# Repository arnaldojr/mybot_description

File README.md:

# mybot_description turtlebot3 Insper

Modelo 3d para simulador Gazebo do robô turtlebot3 com implementações do robô físico do curso de robótica computacional da engenharia de computação Insper.

## Desenvolvido por: Laboratório de informática, lab404.

# Como subir corretamente o robo com a garra no mapa do projeto.

## Atualize os repositorios "my_simulation", "mybot_description" e "robot202" .

    cd ~/catkin_ws/src/my_simulation/ 
    git checkout master
    git stash
    git pull
    cd ~/catkin_ws/src/mybot_descripton
    git checkout master
    git stash
    git pull
    cd ~/catkin_ws/src/robot202
    git pull
    cd ~/catkin_ws
    catkin_make
 
 ## Configure o arquivo .bashrc.
    
    cd ~
    code .bashrc

### Garanta que a configuração das linhas 119 ate 130 estão conforme abaixo:

    #############
    # Robotica  #
    #############

    export IPBerry=192.168.50.35
    # CANCELE  com # as linhas ROS_MASTER_URI  e ROS_IP se estiver usando com Gazebo, Sphinx ou Bebop
    #export ROS_MASTER_URI="http://"$IPBerry":11311" 
    #export ROS_IP=192.168.50.64

    #escolha qual o modelo robo sera usado no simulador
    export TURTLEBOT3_MODEL=burger 
    #export TURTLEBOT3_MODEL=waffle_pi

## Feche todos os terminais e abra um terminal novo

Cada comando deve ser executado em um terminal novo

### abra o mapa do gazebo

    roslaunch my_simulation pista_s.launch
    
### Habilitar controles da garra

    roslaunch mybot_description mybot_control2.launch     
 
### Execute seu codigo python

    rosrun ..........................................

### Como controlar a garra do robô:

A garra do robo é composta de duas partes - braço, pinça- cada parte possui uma articulação, são nestas articulações que atuamos para movimentação.

Joint1 = braço da garra. Valores máximos:

    Garra recolhida: -1.5
    Garra para frente: 0
    Garra levantada: 1.5
    
    rostopic pub -1 /joint1_position_controller/command std_msgs/Float64 "data: 0"

Joint2 = Pinça da garra com mimica (joint2 e joint3 juntos)

    Pinça fechada: 0
    Pinça aberta: -1

    rostopic pub -1 /joint2_position_controller/command std_msgs/Float64 "data: 0"

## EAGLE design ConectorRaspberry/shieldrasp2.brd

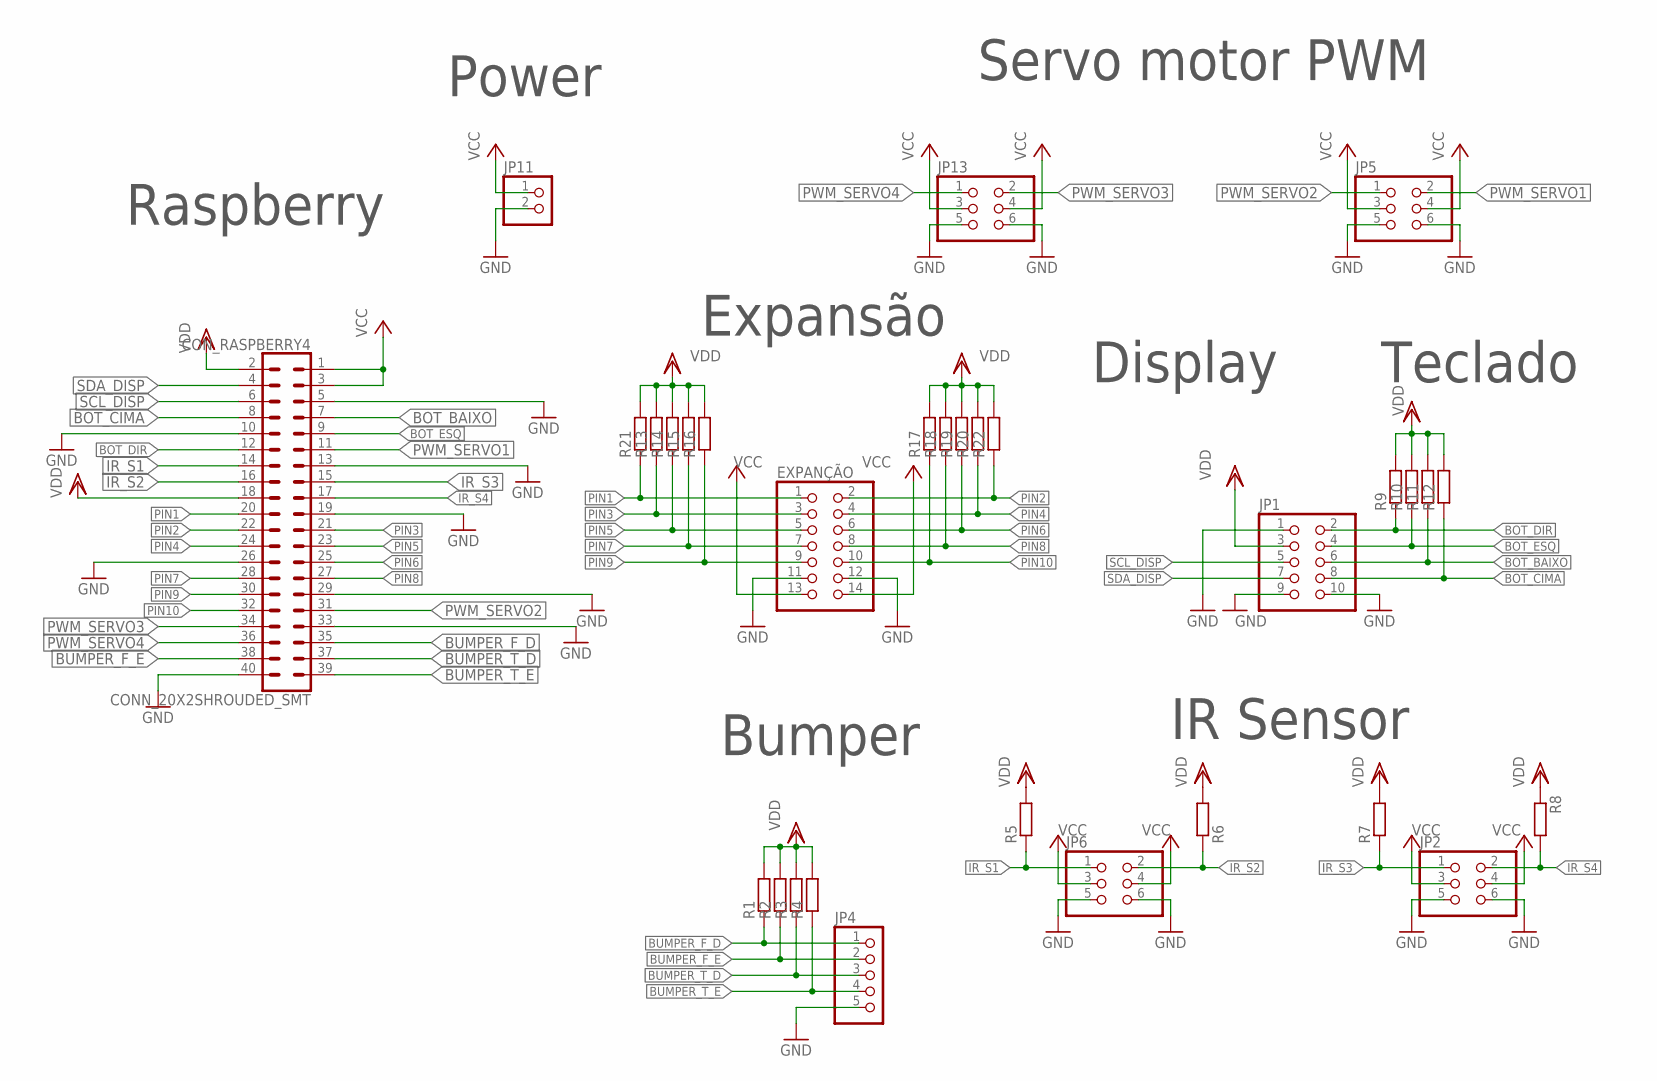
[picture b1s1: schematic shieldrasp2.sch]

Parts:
CON_RASPBERRY4: CONN_20X2SHROUDED_SMT; 2X20_SHROUDED_SMT
EXPANÇÃO: PINHD-2X7; 2X07
JP1: PINHD-2X5/90; 2X05/90
JP2, JP5, JP6, JP13: PINHD-2X3/90; 2X03/90
JP4: PINHD-1X5/90; 1X05/90
JP11: PINHD-1X2/90; 1X02/90
R1, R2, R3, R4, R5, R6, R7, R8, R9, R10, R11, R12, R13, R14, R15, R16, R17, R18, R19, R20, R21, R22: R-EU_M0805; M0805

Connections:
BOT_BAIXO: CON_RASPBERRY4.7, JP1.6, R11.1
BOT_CIMA: CON_RASPBERRY4.8, JP1.8, R12.1
BOT_DIR: CON_RASPBERRY4.12, JP1.2, R9.1
BOT_ESQ: CON_RASPBERRY4.9, JP1.4, R10.1
BUMPER_F_D: CON_RASPBERRY4.35, JP4.1, R1.1
BUMPER_F_E: CON_RASPBERRY4.38, JP4.2, R2.1
BUMPER_T_D: CON_RASPBERRY4.37, JP4.3, R3.1
BUMPER_T_E: CON_RASPBERRY4.39, JP4.4, R4.1
GND: CON_RASPBERRY4.5, CON_RASPBERRY4.10, CON_RASPBERRY4.13, CON_RASPBERRY4.19, CON_RASPBERRY4.26, CON_RASPBERRY4.29, CON_RASPBERRY4.33, CON_RASPBERRY4.40, EXPANÇÃO.11, EXPANÇÃO.12, JP1.1, JP1.9, JP1.10, JP2.5, JP2.6, JP4.5, JP5.5, JP5.6, JP6.5, JP6.6, JP11.2, JP13.5, JP13.6
IR_S1: CON_RASPBERRY4.14, JP6.1, R5.1
IR_S2: CON_RASPBERRY4.16, JP6.2, R6.1
IR_S3: CON_RASPBERRY4.15, JP2.1, R7.1
IR_S4: CON_RASPBERRY4.17, JP2.2, R8.2
PIN1: CON_RASPBERRY4.20, EXPANÇÃO.1, R21.1
PIN2: CON_RASPBERRY4.22, EXPANÇÃO.2, R22.1
PIN3: CON_RASPBERRY4.21, EXPANÇÃO.3, R13.1
PIN4: CON_RASPBERRY4.24, EXPANÇÃO.4, R20.1
PIN5: CON_RASPBERRY4.23, EXPANÇÃO.5, R14.1
PIN6: CON_RASPBERRY4.25, EXPANÇÃO.6, R19.1
PIN7: CON_RASPBERRY4.28, EXPANÇÃO.7, R15.1
PIN8: CON_RASPBERRY4.27, EXPANÇÃO.8, R18.1
PIN9: CON_RASPBERRY4.30, EXPANÇÃO.9, R16.1
PIN10: CON_RASPBERRY4.32, EXPANÇÃO.10, R17.1
PWM_SERVO1: CON_RASPBERRY4.11, JP5.2
PWM_SERVO2: CON_RASPBERRY4.31, JP5.1
PWM_SERVO3: CON_RASPBERRY4.34, JP13.2
PWM_SERVO4: CON_RASPBERRY4.36, JP13.1
SCL_DISP: CON_RASPBERRY4.6, JP1.5
SDA_DISP: CON_RASPBERRY4.4, JP1.7
VCC: CON_RASPBERRY4.1, CON_RASPBERRY4.3, EXPANÇÃO.13, EXPANÇÃO.14, JP2.3, JP2.4, JP5.3, JP5.4, JP6.3, JP6.4, JP11.1, JP13.3, JP13.4
VDD: CON_RASPBERRY4.2, CON_RASPBERRY4.18, JP1.3, R1.2, R2.2, R3.2, R4.2, R5.2, R6.2, R7.2, R8.1, R9.2, R10.2, R11.2, R12.2, R13.2, R14.2, R15.2, R16.2, R17.2, R18.2, R19.2, R20.2, R21.2, R22.2

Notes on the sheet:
Servo motor PWM
Raspberry
Display
Teclado
Bumper
IR Sensor
Power
Expansão

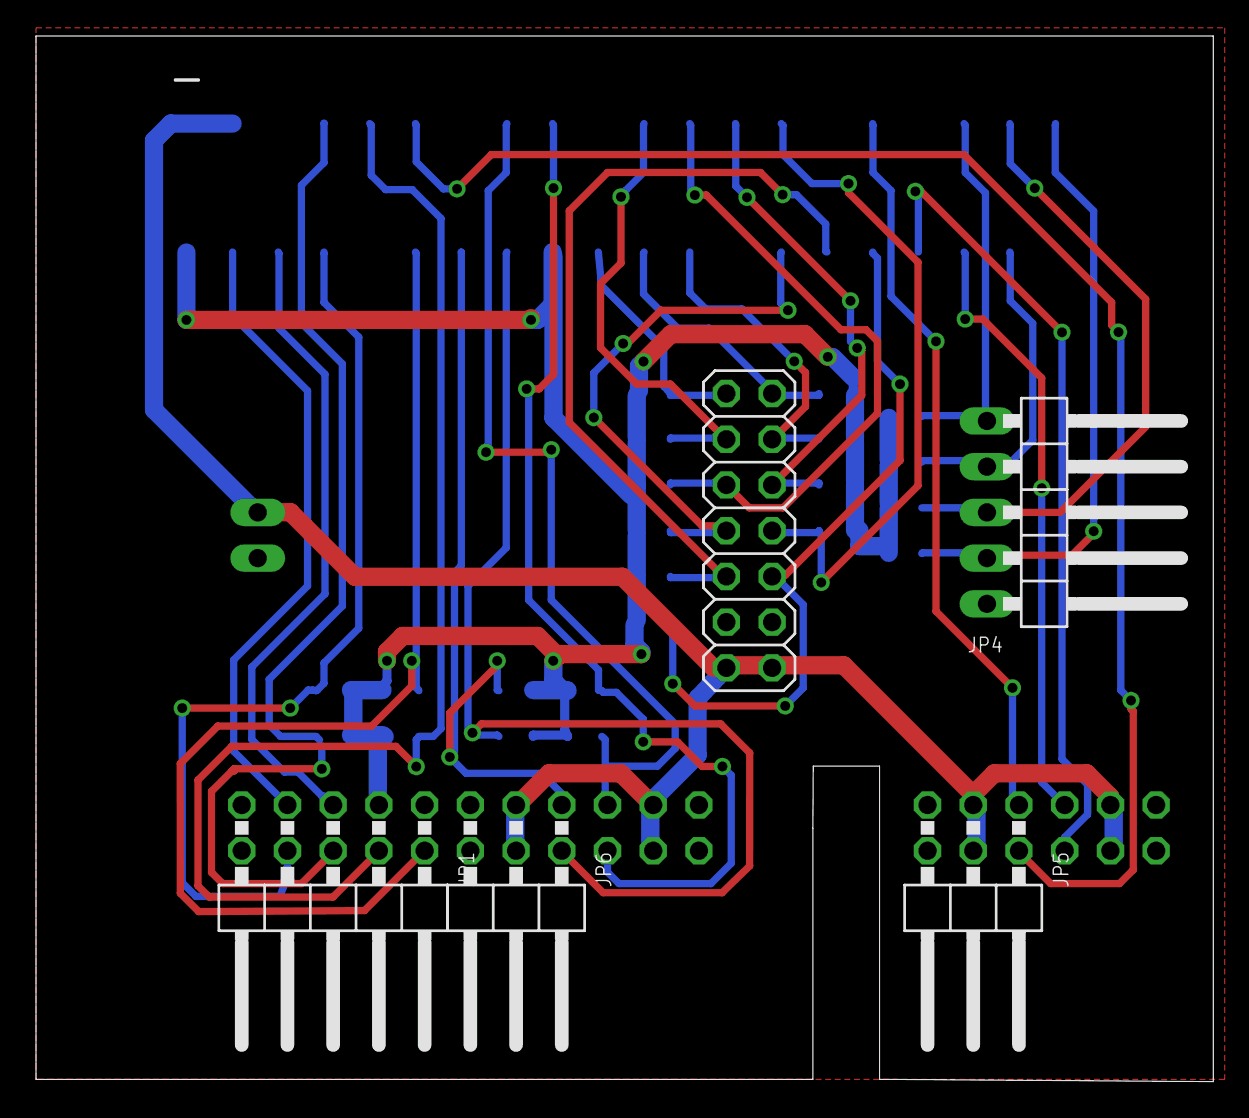
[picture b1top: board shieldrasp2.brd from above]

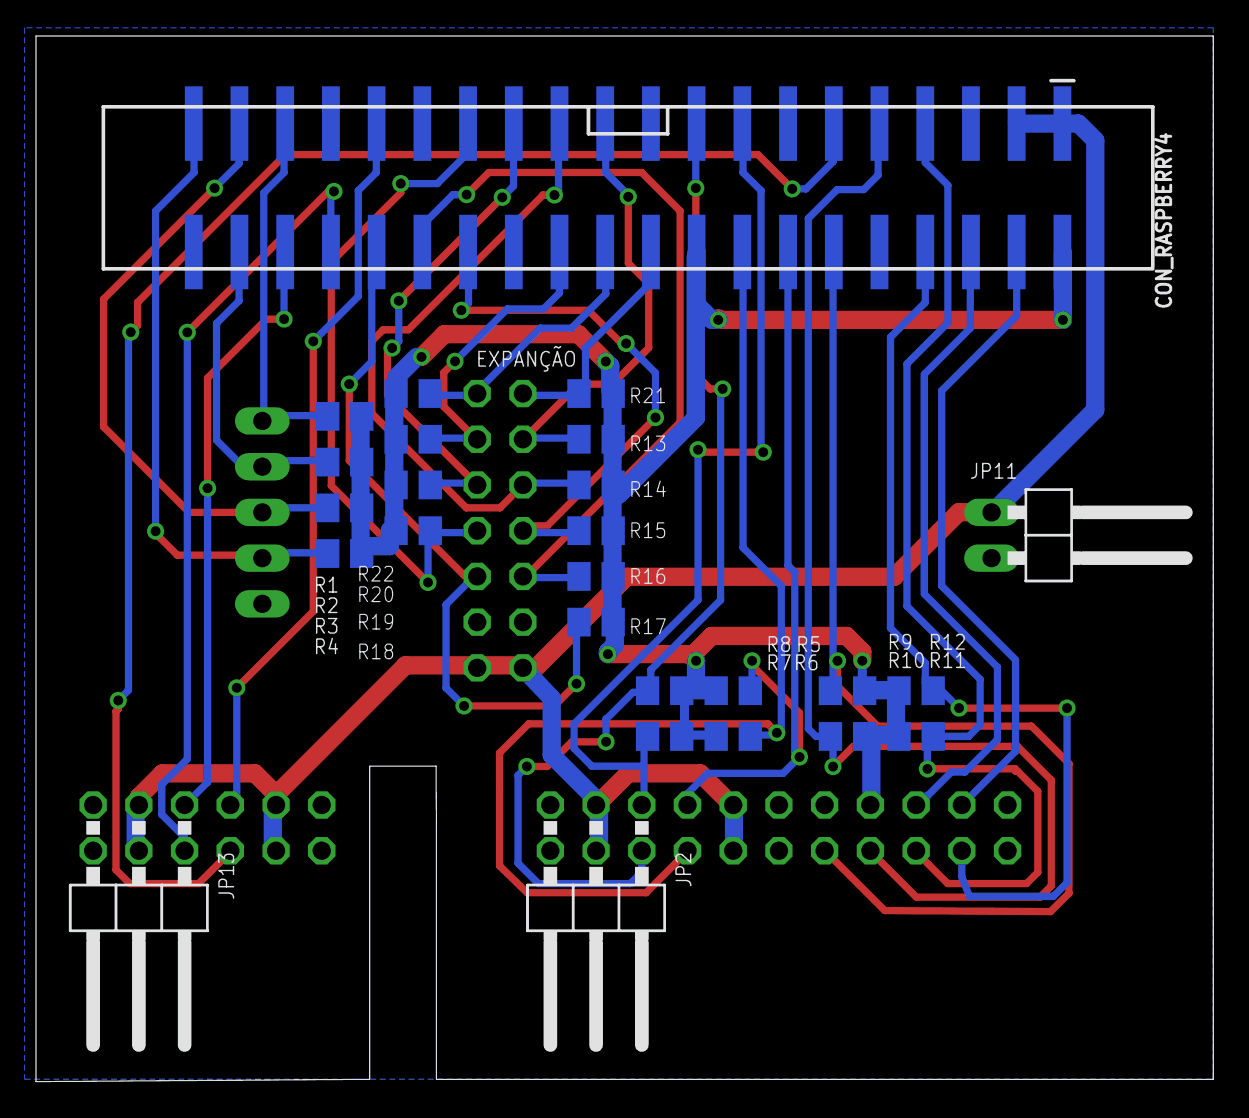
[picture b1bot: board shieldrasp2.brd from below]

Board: 2 copper layers, 65.4 x 58.1 mm, 31 parts (26 on the bottom side), 31 nets.

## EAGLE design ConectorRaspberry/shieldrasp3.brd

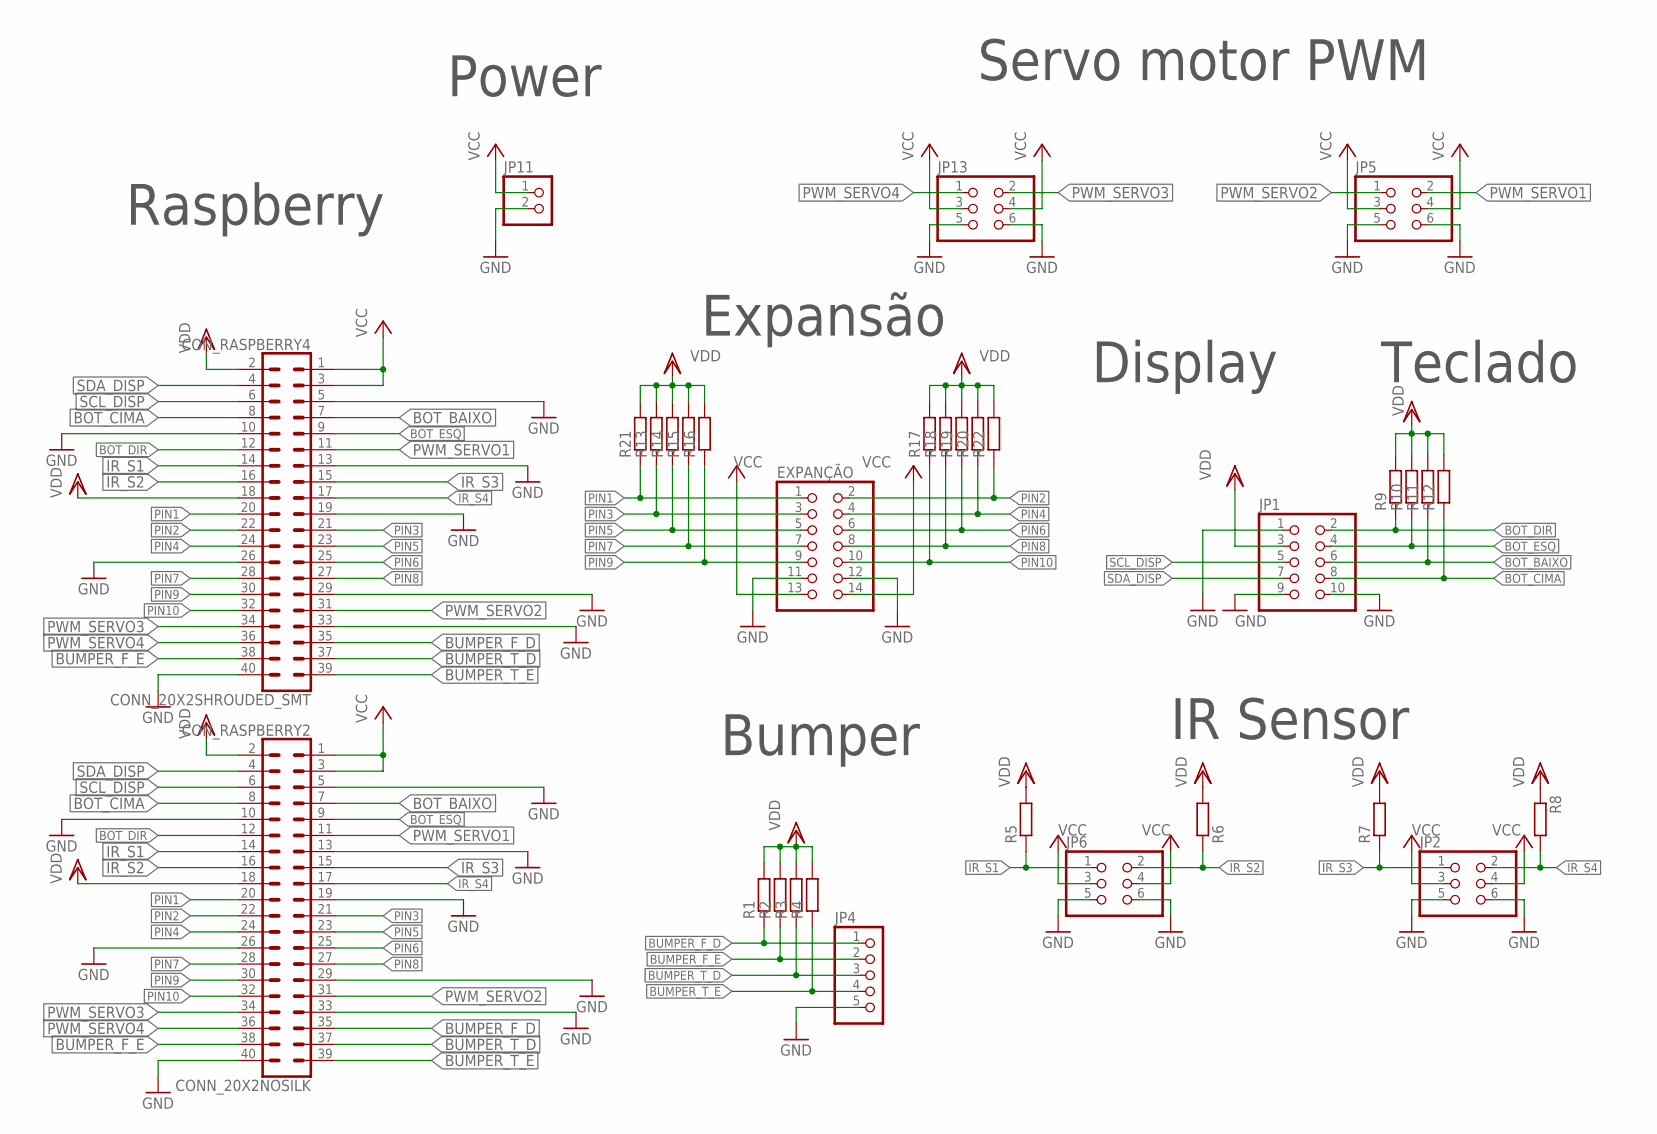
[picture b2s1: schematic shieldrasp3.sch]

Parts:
CON_RASPBERRY2: CONN_20X2NOSILK; 2X20_NOSILK
CON_RASPBERRY4: CONN_20X2SHROUDED_SMT; 2X20_SHROUDED_SMT
EXPANÇÃO: PINHD-2X7; 2X07
JP1: PINHD-2X5; 2X05
JP2, JP5, JP6, JP13: PINHD-2X3; 2X03
JP4: PINHD-1X5; 1X05
JP11: PINHD-1X2; 1X02
R1, R2, R3, R4, R5, R6, R7, R8, R9, R10, R11, R12, R13, R14, R15, R16, R17, R18, R19, R20, R21, R22: R-EU_M0805; M0805

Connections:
BOT_BAIXO: CON_RASPBERRY2.7, CON_RASPBERRY4.7, JP1.6, R11.1
BOT_CIMA: CON_RASPBERRY2.8, CON_RASPBERRY4.8, JP1.8, R12.1
BOT_DIR: CON_RASPBERRY2.12, CON_RASPBERRY4.12, JP1.2, R9.1
BOT_ESQ: CON_RASPBERRY2.9, CON_RASPBERRY4.9, JP1.4, R10.1
BUMPER_F_D: CON_RASPBERRY2.35, CON_RASPBERRY4.35, JP4.1, R1.1
BUMPER_F_E: CON_RASPBERRY2.38, CON_RASPBERRY4.38, JP4.2, R2.1
BUMPER_T_D: CON_RASPBERRY2.37, CON_RASPBERRY4.37, JP4.3, R3.1
BUMPER_T_E: CON_RASPBERRY2.39, CON_RASPBERRY4.39, JP4.4, R4.1
GND: CON_RASPBERRY2.5, CON_RASPBERRY2.10, CON_RASPBERRY2.13, CON_RASPBERRY2.19, CON_RASPBERRY2.26, CON_RASPBERRY2.29, CON_RASPBERRY2.33, CON_RASPBERRY2.40, CON_RASPBERRY4.5, CON_RASPBERRY4.10, CON_RASPBERRY4.13, CON_RASPBERRY4.19, CON_RASPBERRY4.26, CON_RASPBERRY4.29, CON_RASPBERRY4.33, CON_RASPBERRY4.40, EXPANÇÃO.11, EXPANÇÃO.12, JP1.1, JP1.9, JP1.10, JP2.5, JP2.6, JP4.5, JP5.5, JP5.6, JP6.5, JP6.6, JP11.2, JP13.5, JP13.6
IR_S1: CON_RASPBERRY2.14, CON_RASPBERRY4.14, JP6.1, R5.1
IR_S2: CON_RASPBERRY2.16, CON_RASPBERRY4.16, JP6.2, R6.1
IR_S3: CON_RASPBERRY2.15, CON_RASPBERRY4.15, JP2.1, R7.1
IR_S4: CON_RASPBERRY2.17, CON_RASPBERRY4.17, JP2.2, R8.2
PIN1: CON_RASPBERRY2.20, CON_RASPBERRY4.20, EXPANÇÃO.1, R21.1
PIN2: CON_RASPBERRY2.22, CON_RASPBERRY4.22, EXPANÇÃO.2, R22.1
PIN3: CON_RASPBERRY2.21, CON_RASPBERRY4.21, EXPANÇÃO.3, R13.1
PIN4: CON_RASPBERRY2.24, CON_RASPBERRY4.24, EXPANÇÃO.4, R20.1
PIN5: CON_RASPBERRY2.23, CON_RASPBERRY4.23, EXPANÇÃO.5, R14.1
PIN6: CON_RASPBERRY2.25, CON_RASPBERRY4.25, EXPANÇÃO.6, R19.1
PIN7: CON_RASPBERRY2.28, CON_RASPBERRY4.28, EXPANÇÃO.7, R15.1
PIN8: CON_RASPBERRY2.27, CON_RASPBERRY4.27, EXPANÇÃO.8, R18.1
PIN9: CON_RASPBERRY2.30, CON_RASPBERRY4.30, EXPANÇÃO.9, R16.1
PIN10: CON_RASPBERRY2.32, CON_RASPBERRY4.32, EXPANÇÃO.10, R17.1
PWM_SERVO1: CON_RASPBERRY2.11, CON_RASPBERRY4.11, JP5.2
PWM_SERVO2: CON_RASPBERRY2.31, CON_RASPBERRY4.31, JP5.1
PWM_SERVO3: CON_RASPBERRY2.34, CON_RASPBERRY4.34, JP13.2
PWM_SERVO4: CON_RASPBERRY2.36, CON_RASPBERRY4.36, JP13.1
SCL_DISP: CON_RASPBERRY2.6, CON_RASPBERRY4.6, JP1.5
SDA_DISP: CON_RASPBERRY2.4, CON_RASPBERRY4.4, JP1.7
VCC: CON_RASPBERRY2.1, CON_RASPBERRY2.3, CON_RASPBERRY4.1, CON_RASPBERRY4.3, EXPANÇÃO.13, EXPANÇÃO.14, JP2.3, JP2.4, JP5.3, JP5.4, JP6.3, JP6.4, JP11.1, JP13.3, JP13.4
VDD: CON_RASPBERRY2.2, CON_RASPBERRY2.18, CON_RASPBERRY4.2, CON_RASPBERRY4.18, JP1.3, R1.2, R2.2, R3.2, R4.2, R5.2, R6.2, R7.2, R8.1, R9.2, R10.2, R11.2, R12.2, R13.2, R14.2, R15.2, R16.2, R17.2, R18.2, R19.2, R20.2, R21.2, R22.2

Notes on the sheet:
Servo motor PWM
Raspberry
Display
Teclado
Bumper
IR Sensor
Power
Expansão

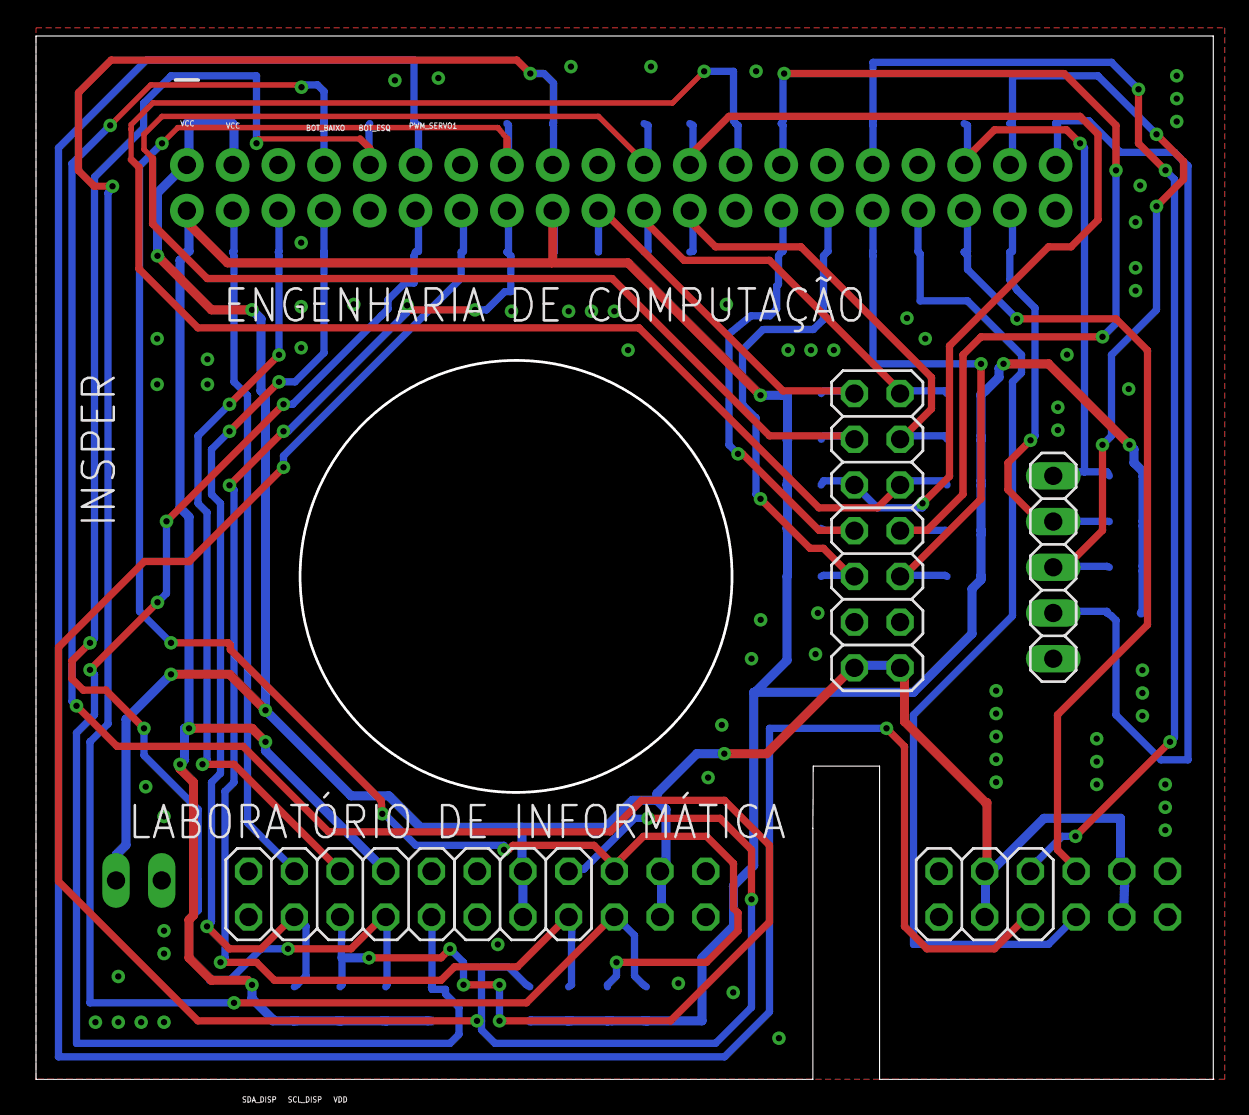
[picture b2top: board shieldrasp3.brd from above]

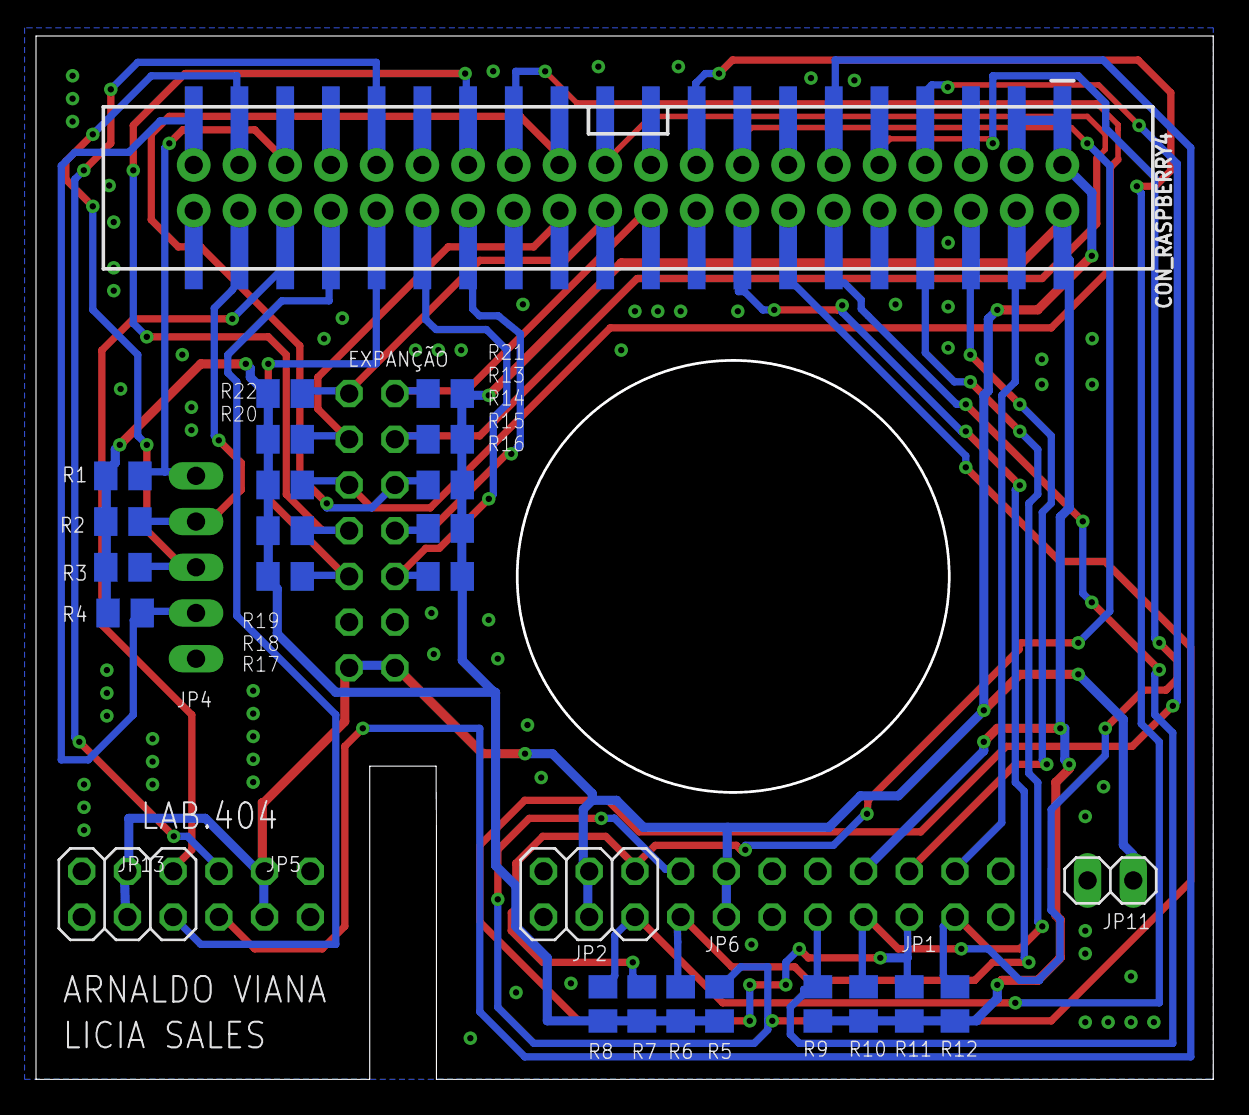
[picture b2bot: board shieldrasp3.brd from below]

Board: 2 copper layers, 65.3 x 57.8 mm, 32 parts (27 on the bottom side), 31 nets.

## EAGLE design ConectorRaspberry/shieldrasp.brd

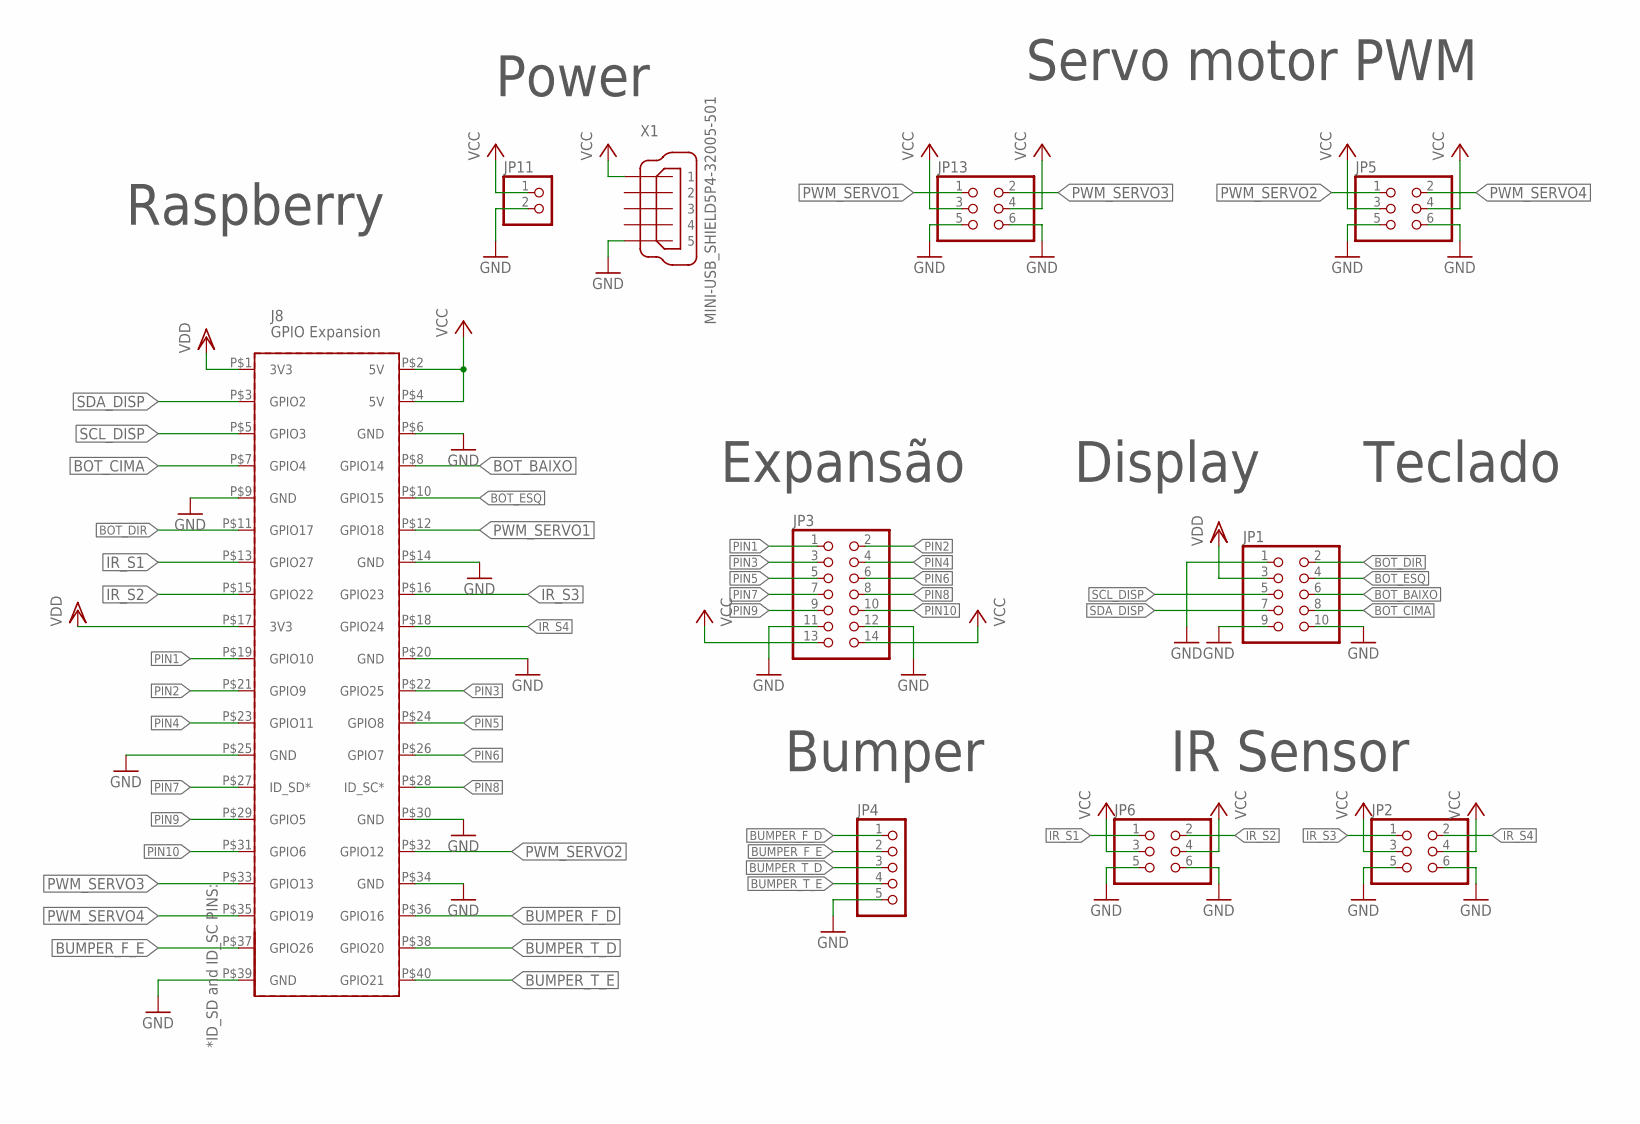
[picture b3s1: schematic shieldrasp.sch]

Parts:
JP1: PINHD-2X5/90; 2X05/90
JP2, JP5, JP6, JP13: PINHD-2X3/90; 2X03/90
JP3: PINHD-2X7; 2X07
JP4: PINHD-1X5/90; 1X05/90
JP11: PINHD-1X2/90; 1X02/90
PCB1: RPI3RPI3; RPI3
X1: MINI-USB_SHIELD5P4-32005-501; 32005-501

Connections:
BOT_BAIXO: JP1.6, PCB1.P$8 (GPIO14)
BOT_CIMA: JP1.8, PCB1.P$7 (GPIO4)
BOT_DIR: JP1.2, PCB1.P$11 (GPIO17)
BOT_ESQ: JP1.4, PCB1.P$10 (GPIO15)
BUMPER_F_D: JP4.1, PCB1.P$36 (GPIO16)
BUMPER_F_E: JP4.2, PCB1.P$37 (GPIO26)
BUMPER_T_D: JP4.3, PCB1.P$38 (GPIO20)
BUMPER_T_E: JP4.4, PCB1.P$40 (GPIO21)
GND: JP1.1, JP1.9, JP1.10, JP2.5, JP2.6, JP3.11, JP3.12, JP4.5, JP5.5, JP5.6, JP6.5, JP6.6, JP11.2, JP13.5, JP13.6, PCB1.P$6 (GND), PCB1.P$9 (GND), PCB1.P$14 (GND), PCB1.P$20 (GND), PCB1.P$25 (GND), PCB1.P$30 (GND), PCB1.P$34 (GND), PCB1.P$39 (GND), X1.5
IR_S1: JP6.1, PCB1.P$13 (GPIO27)
IR_S2: JP6.2, PCB1.P$15 (GPIO22)
IR_S3: JP2.1, PCB1.P$16 (GPIO23)
IR_S4: JP2.2, PCB1.P$18 (GPIO24)
PIN1: JP3.1, PCB1.P$19 (GPIO10)
PIN2: JP3.2, PCB1.P$21 (GPIO9)
PIN3: JP3.3, PCB1.P$22 (GPIO25)
PIN4: JP3.4, PCB1.P$23 (GPIO11)
PIN5: JP3.5, PCB1.P$24 (GPIO8)
PIN6: JP3.6, PCB1.P$26 (GPIO7)
PIN7: JP3.7, PCB1.P$27 (ID_SD*)
PIN8: JP3.8, PCB1.P$28 (ID_SC*)
PIN9: JP3.9, PCB1.P$29 (GPIO5)
PIN10: JP3.10, PCB1.P$31 (GPIO6)
PWM_SERVO1: JP13.1, PCB1.P$12 (GPIO18)
PWM_SERVO2: JP5.1, PCB1.P$32 (GPIO12)
PWM_SERVO3: JP13.2, PCB1.P$33 (GPIO13)
PWM_SERVO4: JP5.2, PCB1.P$35 (GPIO19)
SCL_DISP: JP1.5, PCB1.P$5 (GPIO3)
SDA_DISP: JP1.7, PCB1.P$3 (GPIO2)
VCC: JP2.3, JP2.4, JP3.13, JP3.14, JP5.3, JP5.4, JP6.3, JP6.4, JP11.1, JP13.3, JP13.4, PCB1.P$2 (5V), PCB1.P$4 (5V), X1.1
VDD: JP1.3, PCB1.P$1 (3V3), PCB1.P$17 (3V3)

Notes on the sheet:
Servo motor PWM
Raspberry
Display
Teclado
Bumper
IR Sensor
Power
Expansão

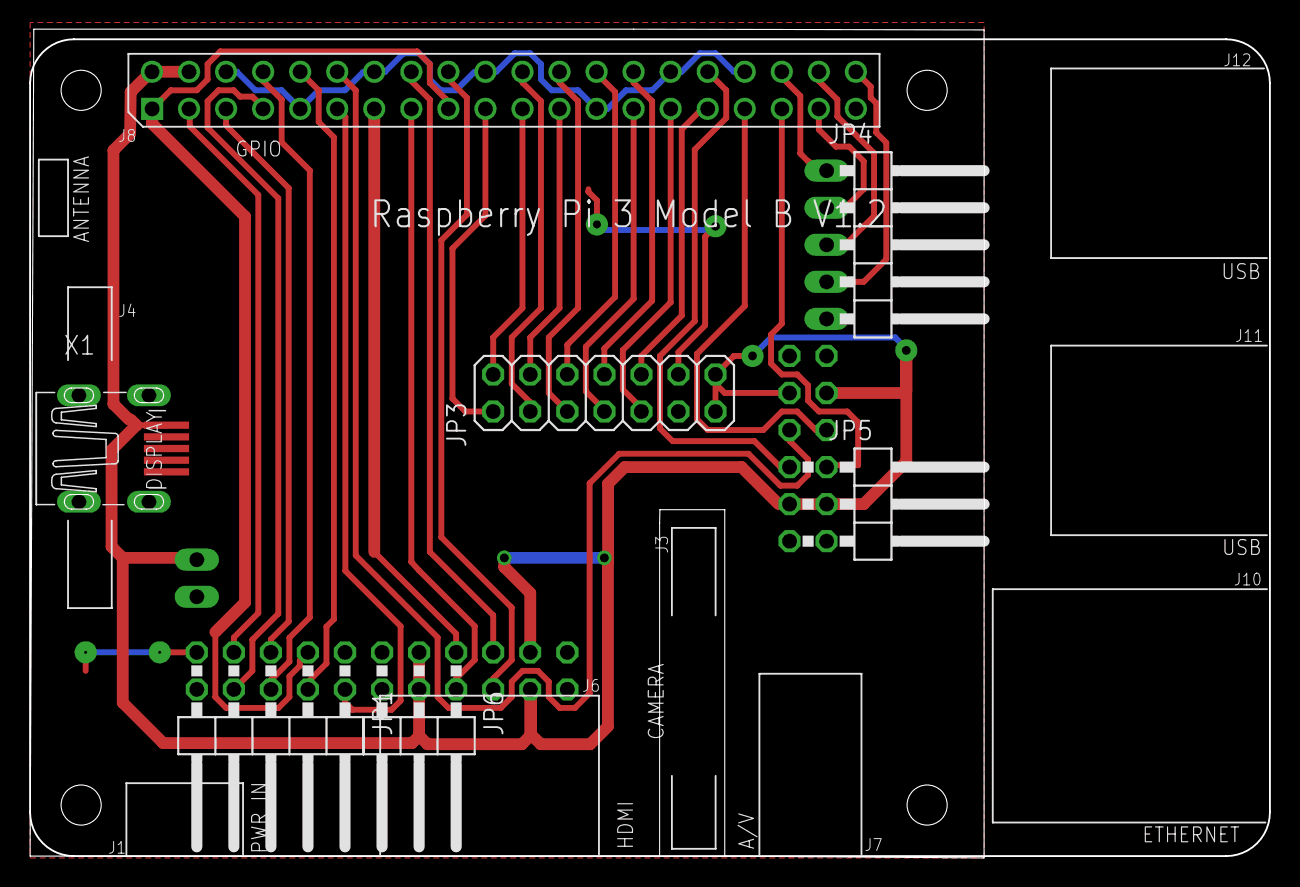
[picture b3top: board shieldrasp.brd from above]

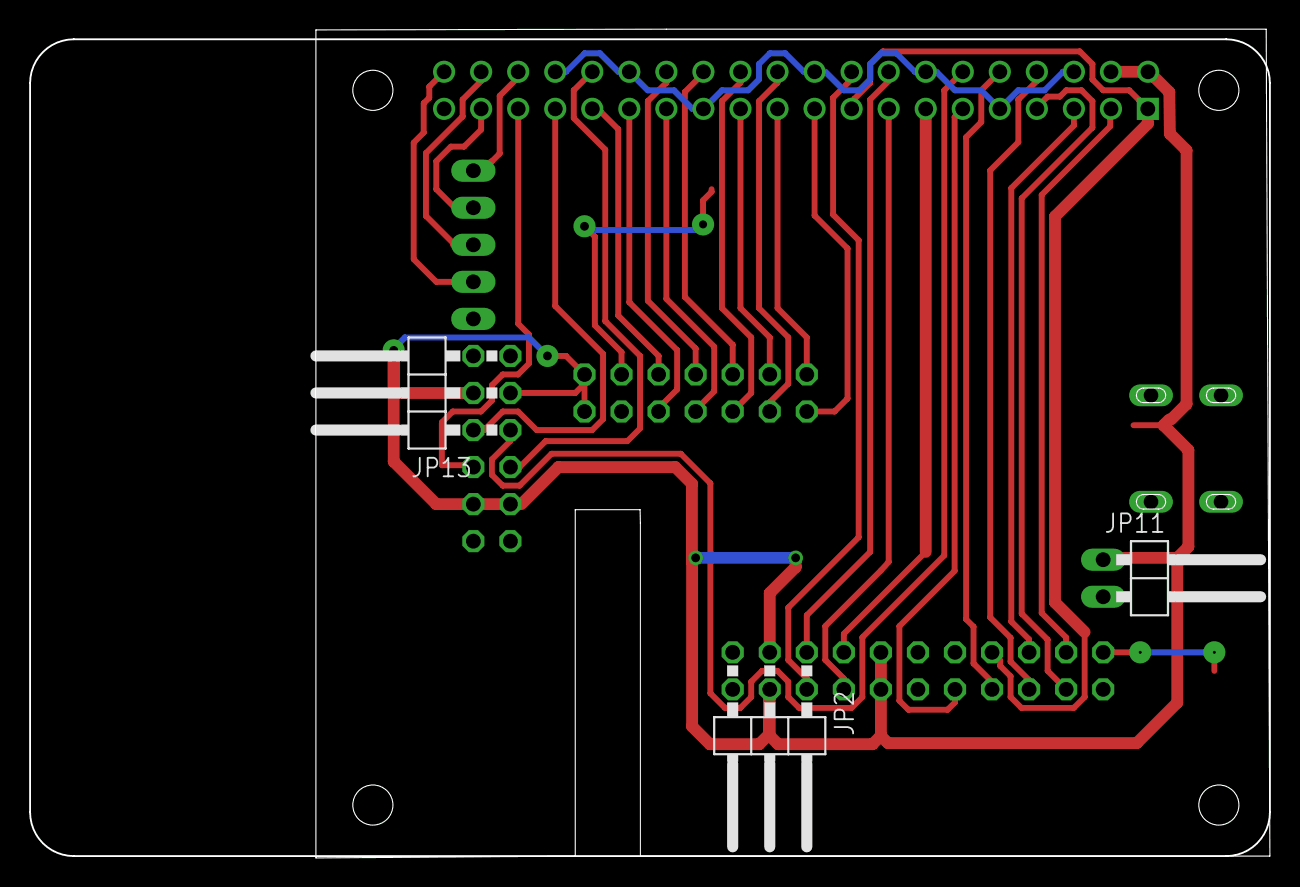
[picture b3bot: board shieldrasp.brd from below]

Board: 2 copper layers, 85.0 x 56.7 mm, 10 parts (3 on the bottom side), 31 nets.

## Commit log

2020-03-26 criado readme.md
2020-03-27 meshs da garra
2020-03-27 bumper
2020-03-30 upgrades in files mybot_garra
2020-03-30 more updates in garra
2020-03-30 correção possiççao camera e bumper
2020-08-26 adc modelos da garrinha no gazebo
2020-08-26 adc o motor e a escala da garra foi ajustada
2020-09-22 atualização garra
2020-09-22 ajuste effort
2020-09-22 ajuste posição camera e garra
2020-09-22 atualização urfd garra
2020-09-22 atualização garra turtle
2020-09-28 fix pid and colors
2020-09-28 change image README
2020-09-28 gazebo e rviz publicando
2020-09-28 garra mimica ok e gazebo e rviz
2020-10-01 ajuste PID, ajuste base_link, correção launch joint state
2020-10-01 atualização readme
2020-10-01 ajuste atrito
2020-10-19 garrinha pintada de verde
2022-05-03 up yaml
2022-05-20 subindo os urdfs
2022-06-30 shield rasp4 turtlebot
    arquivos shield rasp4 para o turtlebotinsper, software Eagle PCB

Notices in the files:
parts and their libraries:
SparkFun-Connectors: Licensing: Creative Commons ShareAlike 4.0 International - https://creativecommons.org/licenses/by-sa/4.0
